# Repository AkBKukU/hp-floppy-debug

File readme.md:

# Floppy Poser

**UNTESTED DESIGN**
*This board has not been produced and ordered yet. The software to drive it doesn't even exist at this time. DO NOT BUILD THIS!*

## What this technically is

This is a ground up redo of my [Floppy Switch Board](https://github.com/AkBKukU/FloppySwitchBoard) that is controlled by an Arduino instead of a switch. Additionally, it uses buffer chips to switch more than before and can switch between two different drive pairs entirely.

## What this really is

I'm working towards a larger project and needed a test bed for a few concepts and the amility to probe a floppy bus with an HP probe pod directly. So this has some more features related to that which are useless for anyone else.

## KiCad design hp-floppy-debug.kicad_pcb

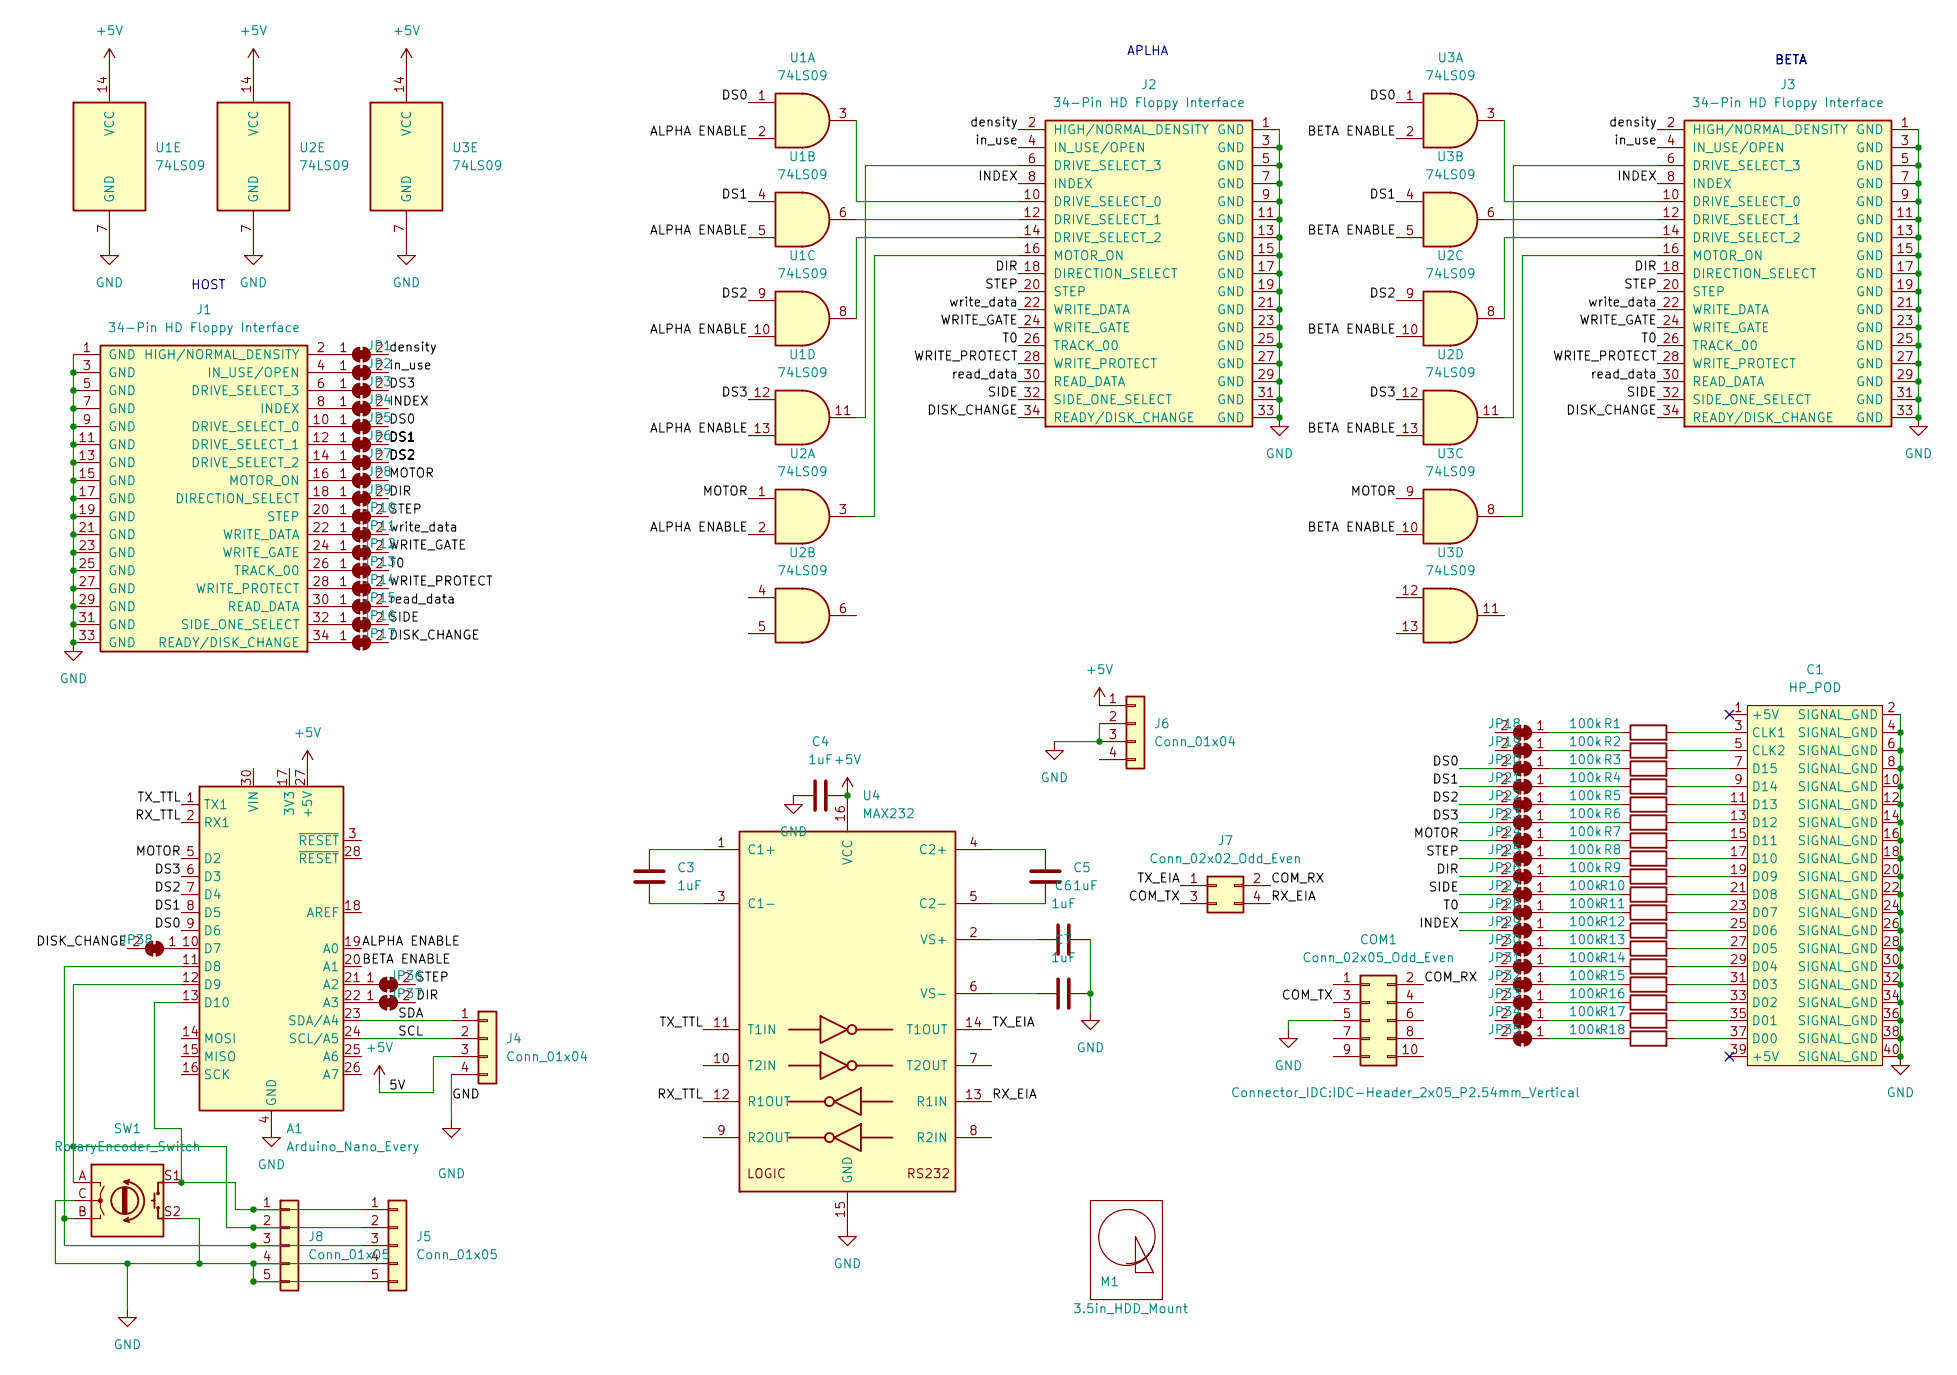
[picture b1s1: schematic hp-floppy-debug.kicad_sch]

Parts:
A1: Arduino_Nano_Every; Arduino_Nano
C1: HP_POD; HP Probe POD; Manufacturer Part Number 302-S401
C3, C4, C5, C6, C7: 1uF; C_1206_3216Metric_Pad1.33x1.80mm_HandSolder; Manufacturer Part Number GMC31X7R105M100NT
COM1: Conn_02x05_Odd_Even; IDC-Header_2x05_P2.54mm_Vertical; Manufacturer Part Number CH87102V200
J1, J2, J3: 34-Pin HD Floppy Interface; IDC-Header_2x17_P2.54mm_Vertical; Manufacturer Part Number 302-S341
J4: Conn_01x04; PinHeader_1x04_P2.54mm_Vertical
J5, J8: Conn_01x05; PinHeader_1x05_P2.54mm_Vertical
J6: Conn_01x04; PinHeader_1x04_P2.54mm_Horizontal; Manufacturer Part Number 171826-4
J7: Conn_02x02_Odd_Even; PinHeader_2x02_P2.54mm_Vertical
JP1, JP2, JP3, JP4, JP5, JP6, JP7, JP8, JP9, JP10, JP11, JP12, JP13, JP14, JP15, JP16, JP17, JP18, JP19, JP20, JP21, JP22, JP23, JP24, JP25, JP26, JP27, JP28, JP29, JP30, JP31, JP32, JP33, JP34, JP35, JP36, JP37, JP38: SolderJumper_2_Bridged; SolderJumper-2_P1.3mm_Bridged_RoundedPad1.0x1.5mm
M1: 3.5in_HDD_Mount; 3.5in HDD Bottom Mount
R1, R2, R3, R4, R5, R6, R7, R8, R9, R10, R11, R12, R13, R14, R15, R16, R17, R18: 100k; R_0603_1608Metric_Pad0.98x0.95mm_HandSolder; Manufacturer Part Number RC0603FR-7W100KL
SW1: RotaryEncoder_Switch; RotaryEncoder_Alps_EC11E-Switch_Vertical_H20mm; Manufacturer Part Number PEC11R-4220K-S0024
U1, U2, U3: 74LS09; DIP-14_W10.16mm_LongPads; Manufacturer Part Number SN74LS09N
U4: MAX232; SOIC-16_3.9x9.9mm_P1.27mm; Manufacturer Part Number MAX232DR

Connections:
+5V: A1.27 (+5V), C4.1, J4.3, J6.1, U1.14 (VCC), U2.14 (VCC), U3.14 (VCC), U4.16 (VCC)
/ALPHA ENABLE: A1.19 (A0), U1.2, U1.5, U1.10, U1.13, U2.2
/BETA ENABLE: A1.20 (A1), U2.10, U2.13, U3.2, U3.5, U3.10
/COM_RX: COM1.2, J7.2
/COM_TX: COM1.3, J7.3
/DIR: J2.18 (DIRECTION_SELECT), J3.18 (DIRECTION_SELECT), JP9.2 (B), JP26.2 (B), JP37.2 (B)
/DISK_CHANGE: J2.34 (READY/DISK_CHANGE), J3.34 (READY/DISK_CHANGE), JP17.2 (B), JP38.2 (B)
/DS0: A1.9 (D6), JP5.2 (B), JP20.2 (B), U1.1, U3.1
/DS1: A1.8 (D5), JP6.2 (B), JP21.2 (B), U1.4, U3.4
/DS2: A1.7 (D4), JP7.2 (B), JP22.2 (B), U1.9, U2.9
/DS3: A1.6 (D3), JP3.2 (B), JP23.2 (B), U1.12, U2.12
/INDEX: J2.8 (INDEX), J3.8 (INDEX), JP4.2 (B), JP29.2 (B)
/MOTOR: A1.5 (D2), JP8.2 (B), JP24.2 (B), U2.1, U3.9
/RX_EIA: J7.4, U4.13 (R1IN)
/RX_TTL: A1.2 (RX1), U4.12 (R1OUT)
/SCL: A1.24 (SCL/A5), J4.2
/SDA: A1.23 (SDA/A4), J4.1
/SIDE: J2.32 (SIDE_ONE_SELECT), J3.32 (SIDE_ONE_SELECT), JP16.2 (B), JP27.2 (B)
/STEP: J2.20 (STEP), J3.20 (STEP), JP10.2 (B), JP25.2 (B), JP36.2 (B)
/T0: J2.26 (TRACK_00), J3.26 (TRACK_00), JP13.2 (B), JP28.2 (B)
/TX_EIA: J7.1, U4.14 (T1OUT)
/TX_TTL: A1.1 (TX1), U4.11 (T1IN)
/WRITE_GATE: J2.24 (WRITE_GATE), J3.24 (WRITE_GATE), JP12.2 (B)
/WRITE_PROTECT: J2.28 (WRITE_PROTECT), J3.28 (WRITE_PROTECT), JP14.2 (B)
/density: J2.2 (HIGH/NORMAL_DENSITY), J3.2 (HIGH/NORMAL_DENSITY), JP1.2 (B)
/in_use: J2.4 (IN_USE/OPEN), J3.4 (IN_USE/OPEN), JP2.2 (B)
/read_data: J2.30 (READ_DATA), J3.30 (READ_DATA), JP15.2 (B)
/write_data: J2.22 (WRITE_DATA), J3.22 (WRITE_DATA), JP11.2 (B)
GND: A1.4 (GND), A1.29 (GND), C1.2 (SIGNAL_GND), C1.4 (SIGNAL_GND), C1.6 (SIGNAL_GND), C1.8 (SIGNAL_GND), C1.10 (SIGNAL_GND), C1.12 (SIGNAL_GND), C1.14 (SIGNAL_GND), C1.16 (SIGNAL_GND), C1.18 (SIGNAL_GND), C1.20 (SIGNAL_GND), C1.22 (SIGNAL_GND), C1.24 (SIGNAL_GND), C1.26 (SIGNAL_GND), C1.28 (SIGNAL_GND), C1.30 (SIGNAL_GND), C1.32 (SIGNAL_GND), C1.34 (SIGNAL_GND), C1.36 (SIGNAL_GND), C1.38 (SIGNAL_GND), C1.40 (SIGNAL_GND), C4.2, C6.2, C7.2, COM1.5, J1.1 (GND), J1.3 (GND), J1.5 (GND), J1.7 (GND), J1.9 (GND), J1.11 (GND), J1.13 (GND), J1.15 (GND), J1.17 (GND), J1.19 (GND), J1.21 (GND), J1.23 (GND), J1.25 (GND), J1.27 (GND), J1.29 (GND), J1.31 (GND), J1.33 (GND), J2.1 (GND), J2.3 (GND), J2.5 (GND), J2.7 (GND), J2.9 (GND), J2.11 (GND), J2.13 (GND), J2.15 (GND), J2.17 (GND), J2.19 (GND), J2.21 (GND), J2.23 (GND), J2.25 (GND), J2.27 (GND), J2.29 (GND), J2.31 (GND), J2.33 (GND), J3.1 (GND), J3.3 (GND), J3.5 (GND), J3.7 (GND), J3.9 (GND), J3.11 (GND), J3.13 (GND), J3.15 (GND), J3.17 (GND), J3.19 (GND), J3.21 (GND), J3.23 (GND), J3.25 (GND), J3.27 (GND), J3.29 (GND), J3.31 (GND), J3.33 (GND), J4.4, J5.4, J5.5, J6.2, J6.3, J8.4, J8.5, SW1.C, SW1.S2, U1.7 (GND), U2.7 (GND), U3.7 (GND), U4.15 (GND)
unnamed: A1.10 (D7), JP38.1 (A)
unnamed: A1.11 (D8), J5.3, J8.3, SW1.B
unnamed: A1.12 (D9), J5.2, J8.2, SW1.A
unnamed: A1.13 (D10), J5.1, J8.1, SW1.S1
unnamed: A1.21 (A2), JP36.1 (A)
unnamed: A1.22 (A3), JP37.1 (A)
unnamed: C1.3 (CLK1), R1.2
unnamed: C1.5 (CLK2), R2.2
unnamed: C1.7 (D15), R3.2
unnamed: C1.9 (D14), R4.2
unnamed: C1.11 (D13), R5.2
unnamed: C1.13 (D12), R6.2
unnamed: C1.15 (D11), R7.2
unnamed: C1.17 (D10), R8.2
unnamed: C1.19 (D09), R9.2
unnamed: C1.21 (D08), R10.2
unnamed: C1.23 (D07), R11.2
unnamed: C1.25 (D06), R12.2
unnamed: C1.27 (D05), R13.2
unnamed: C1.29 (D04), R14.2
unnamed: C1.31 (D03), R15.2
unnamed: C1.33 (D02), R16.2
unnamed: C1.35 (D01), R17.2
unnamed: C1.37 (D00), R18.2
unnamed: C3.1, U4.1 (C1+)
unnamed: C3.2, U4.3 (C1-)
unnamed: C5.1, U4.4 (C2+)
unnamed: C5.2, U4.5 (C2-)
unnamed: C6.1, U4.2 (VS+)
unnamed: C7.1, U4.6 (VS-)
unnamed: J1.2 (HIGH/NORMAL_DENSITY), JP1.1 (A)
unnamed: J1.4 (IN_USE/OPEN), JP2.1 (A)
unnamed: J1.6 (DRIVE_SELECT_3), JP3.1 (A)
unnamed: J1.8 (INDEX), JP4.1 (A)
unnamed: J1.10 (DRIVE_SELECT_0), JP5.1 (A)
unnamed: J1.12 (DRIVE_SELECT_1), JP6.1 (A)
unnamed: J1.14 (DRIVE_SELECT_2), JP7.1 (A)
unnamed: J1.16 (MOTOR_ON), JP8.1 (A)
unnamed: J1.18 (DIRECTION_SELECT), JP9.1 (A)
unnamed: J1.20 (STEP), JP10.1 (A)
unnamed: J1.22 (WRITE_DATA), JP11.1 (A)
unnamed: J1.24 (WRITE_GATE), JP12.1 (A)
unnamed: J1.26 (TRACK_00), JP13.1 (A)
unnamed: J1.28 (WRITE_PROTECT), JP14.1 (A)
unnamed: J1.30 (READ_DATA), JP15.1 (A)
unnamed: J1.32 (SIDE_ONE_SELECT), JP16.1 (A)
unnamed: J1.34 (READY/DISK_CHANGE), JP17.1 (A)
unnamed: J2.6 (DRIVE_SELECT_3), U1.11
unnamed: J2.10 (DRIVE_SELECT_0), U1.3
unnamed: J2.12 (DRIVE_SELECT_1), U1.6
unnamed: J2.14 (DRIVE_SELECT_2), U1.8
unnamed: J2.16 (MOTOR_ON), U2.3
unnamed: J3.6 (DRIVE_SELECT_3), U2.11
unnamed: J3.10 (DRIVE_SELECT_0), U3.3
unnamed: J3.12 (DRIVE_SELECT_1), U3.6
unnamed: J3.14 (DRIVE_SELECT_2), U2.8
unnamed: J3.16 (MOTOR_ON), U3.8
unnamed: JP18.1 (A), R1.1
unnamed: JP19.1 (A), R2.1
unnamed: JP20.1 (A), R3.1
unnamed: JP21.1 (A), R4.1
unnamed: JP22.1 (A), R5.1
unnamed: JP23.1 (A), R6.1
unnamed: JP24.1 (A), R7.1
unnamed: JP25.1 (A), R8.1
unnamed: JP26.1 (A), R9.1
unnamed: JP27.1 (A), R10.1
unnamed: JP28.1 (A), R11.1
unnamed: JP29.1 (A), R12.1
unnamed: JP30.1 (A), R13.1
unnamed: JP31.1 (A), R14.1
unnamed: JP32.1 (A), R15.1
unnamed: JP33.1 (A), R16.1
unnamed: JP34.1 (A), R17.1
unnamed: JP35.1 (A), R18.1

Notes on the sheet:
HOST
BETA
APLHA

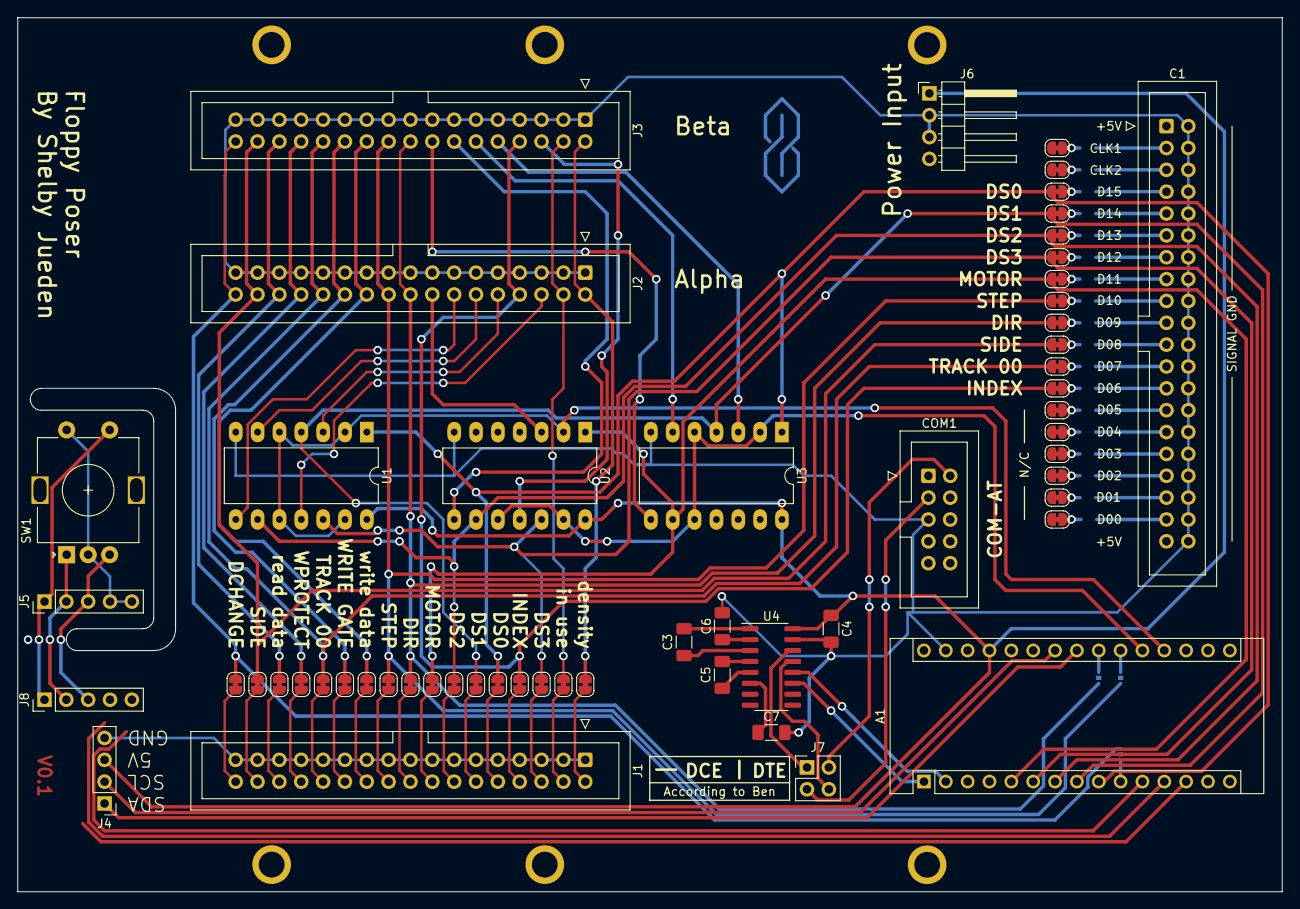
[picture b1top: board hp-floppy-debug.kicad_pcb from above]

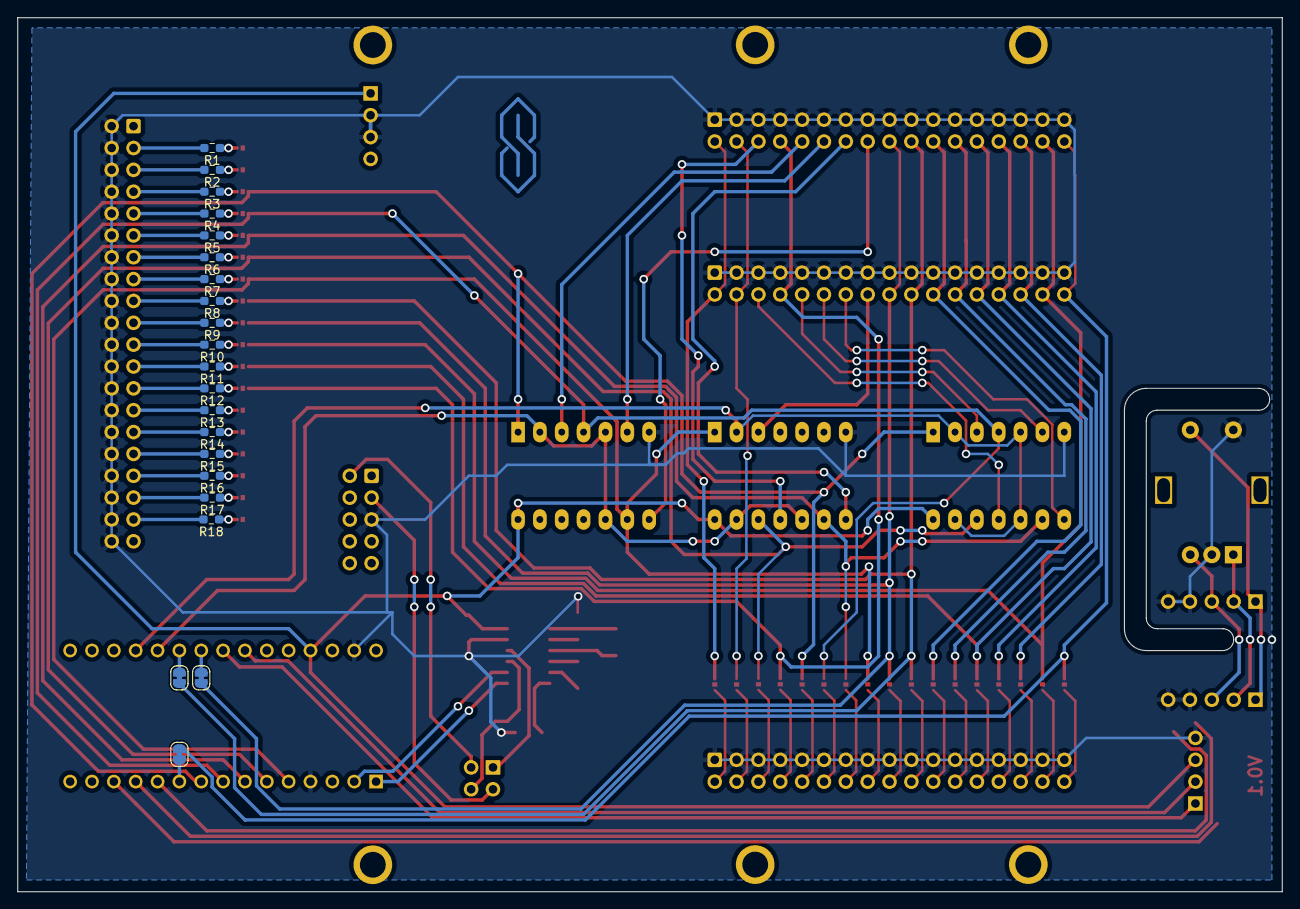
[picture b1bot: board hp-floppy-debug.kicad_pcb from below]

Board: 2 copper layers, 147.0 x 101.6 mm, 78 parts (21 on the bottom side), 104 nets.

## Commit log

2024-11-15 init
2024-11-15 fix image
2024-11-15 review changes
2024-11-16 Remove unconnected trace
